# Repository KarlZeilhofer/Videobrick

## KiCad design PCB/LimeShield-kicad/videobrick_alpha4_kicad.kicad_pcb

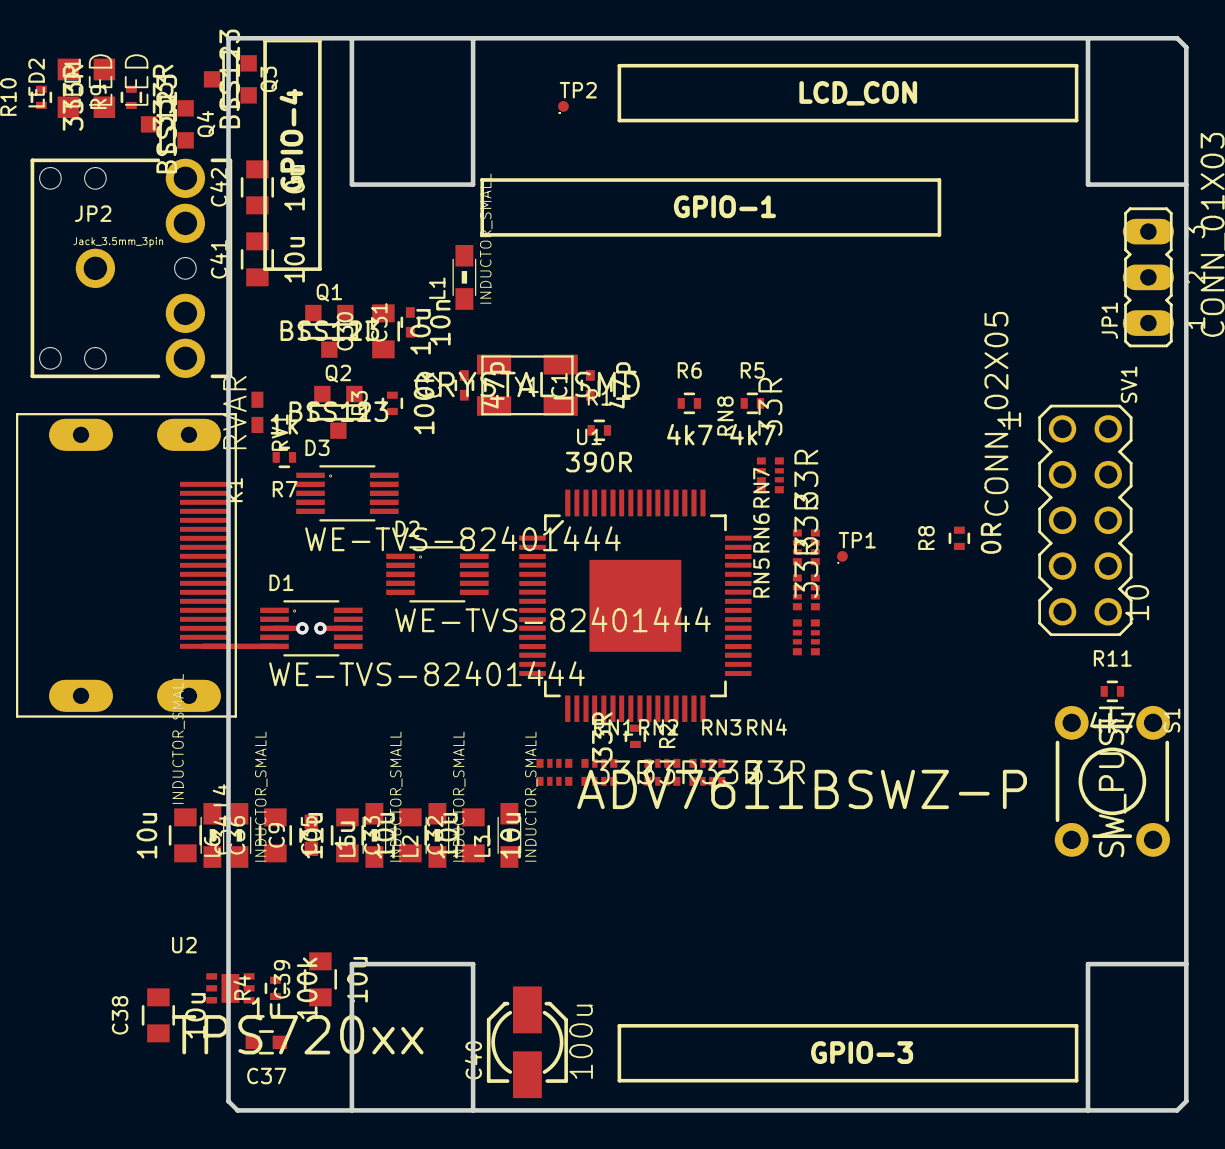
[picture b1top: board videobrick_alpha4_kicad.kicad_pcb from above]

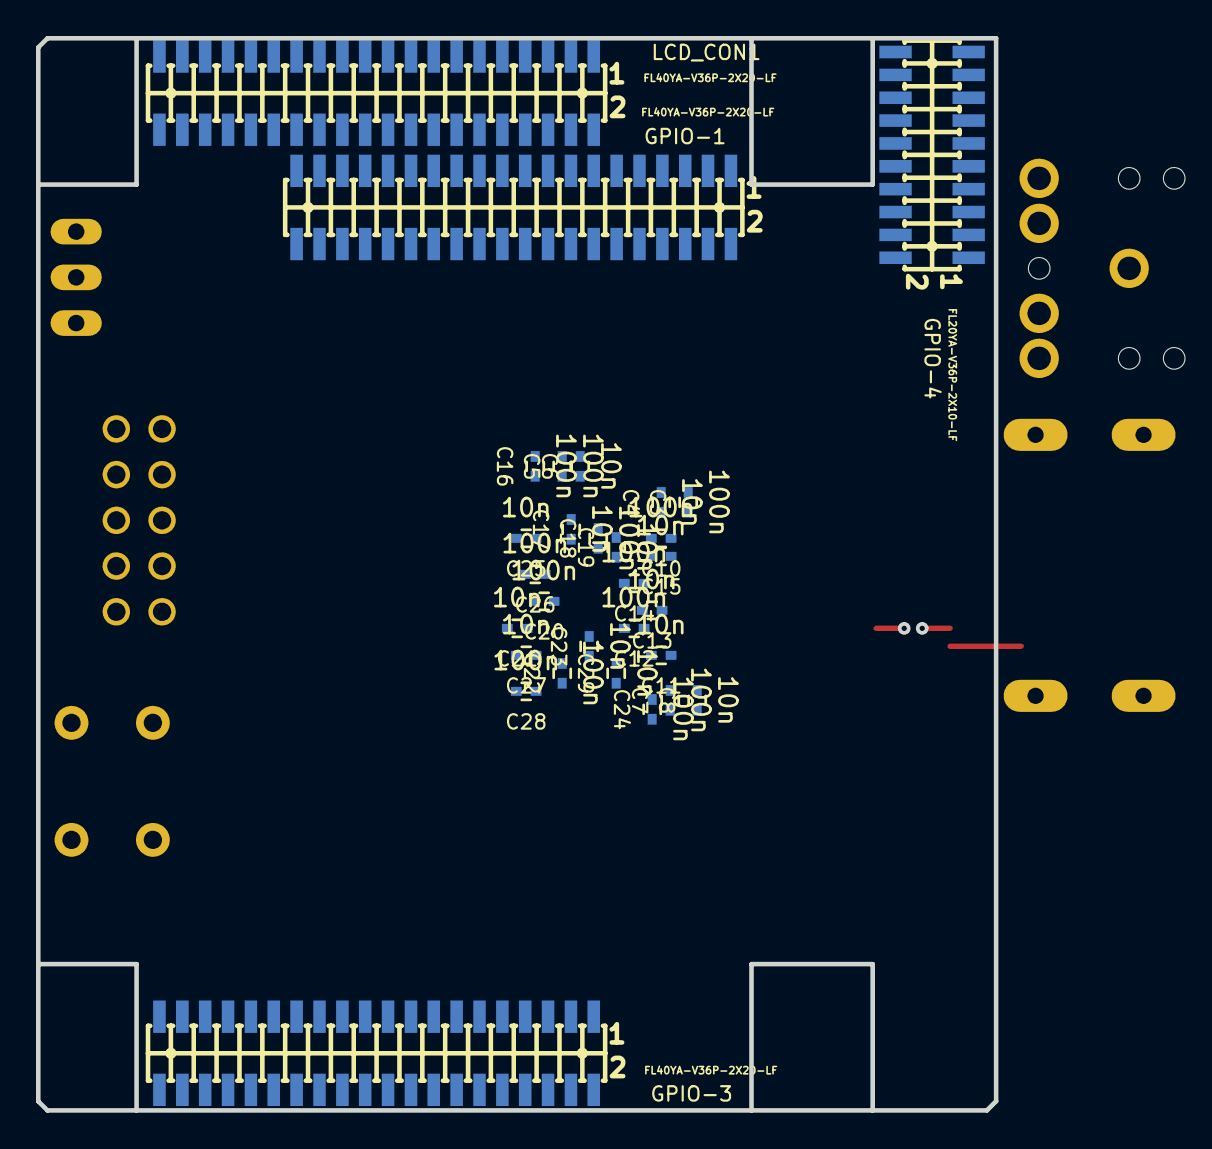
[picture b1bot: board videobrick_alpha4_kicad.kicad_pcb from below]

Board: 4 copper layers, 53.2 x 59.6 mm, 91 parts (30 on the bottom side), 108 nets.

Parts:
C1, C2: 47p; C_0402
C3, C5, C7, C10, C12, C14, C16, C18, C20, C22, C24, C26, C28: 100n; C_0402
C4, C6, C8, C11, C13, C15, C17, C19, C21, C23, C25, C27, C29, C31: 10n; C_0402
C9, C37: 1u; C_0603
C30, C32, C33, C34, C35, C36, C38, C39, C41, C42: 10u; C_0805
C40: 100u; RCL_153CLV-0405
D1, D2, D3: WE-TVS-82401444; WE-TVS_82401444_WE-TVS_MSOP-10L
GPIO-1, GPIO-3: FL40YA-V36P-2X20-LF; A10_OLIMEXINO_LIME_SHIELD_1-YA-V36P-2X20-LF
GPIO-4: FL20YA-V36P-2X10-LF; A10_OLIMEXINO_LIME_SHIELD_1-YA-V36P-2X10-LF
JP1: CONN_01X03; JUMPER_JP2
JP2: Jack_3.5mm_3pin; SPARKFUN-CONNECTORS_AUDIO-JACK
K1: WE-685119134923; INPUTOUTPUTIO_685119134923
L1, L2, L3, L4, L5, L6: INDUCTOR_SMALL; WE-CBF_0805
LCD_CON1: FL40YA-V36P-2X20-LF; A10_OLIMEXINO_LIME_SHIELD_1-YA-V36P-2X20-LF
LED1, LED2: LED; LED_CHIPLED_0805
Q1, Q2, Q3, Q4: BSS123; SOT-23-GDS
R1: 390R; R_0402
R2: 33R; R_0402
R3, R4: 100k; R_0402
R5, R6, R11: 4k7; R_0402
R7: 1k; R_0402
R8: 0R; R_0402
R9, R10: 333R; R_0402
RN1, RN2, RN3, RN4, RN5, RN6, RN7, RN8: 33R; RESISTOR-DIL_4X0402ARV341
RV1: RVAR; WE-VS_WESURGE_0402
S1: SW_PUSH; SPARKFUN-ELECTROMECHANICAL_TACTILE-PTH
SV1: CONN_02X05; CON-LSTB_MA05-2
TP1: TST; TESTPAD_TP06R
TP2: MCLK; TESTPAD_TP06R
U1: ADV7611BSWZ-P; ADI-PHASE-2_QFP50P1200X1200X160-65N
U2: TPS720xx; TEXAS-INSTRUMENTS_BY_ELEMENT14_BATCH_1_SON65P200X200X80-7N
Y1: CRYSTAL_SMD; XTALS_5MM_3.2MM

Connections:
+3.3V: C39.1, D1.3, D2.3, D3.3, GPIO-1.3, GPIO-3.3, GPIO-4.1, L2.1, L3.1, LCD_CON1.3, R4.1, R5.1, R6.1, R9.1, R10.1, R11.1, SV1.10, U2.4, U2.6
+5V: GPIO-1.1, L1.1, LCD_CON1.1
/Connectors/ADV7611_INT: GPIO-3.7, U1.55
/Connectors/ADV7611_RESET: GPIO-1.38, U1.56
/Connectors/ADV7611_SCL: GPIO-1.36, JP1.2, R5.2, U1.53
/Connectors/ADV7611_SDA: GPIO-1.34, JP1.3, R6.2, U1.54
/Connectors/CSI1_D0: GPIO-1.13, RN6.8
/Connectors/CSI1_D1: GPIO-1.15, RN6.7
/Connectors/CSI1_D2: GPIO-1.17, RN6.6
/Connectors/CSI1_D3: GPIO-1.19, RN6.5
/Connectors/CSI1_D4: GPIO-1.21, RN5.8
/Connectors/CSI1_D5: GPIO-1.23, RN5.7
/Connectors/CSI1_D6: GPIO-1.25, RN5.6
/Connectors/CSI1_D7: GPIO-1.27, RN5.5
/Connectors/CSI1_D9: GPIO-3.11, RN4.7
/Connectors/CSI1_D10: GPIO-3.13, RN4.6
/Connectors/CSI1_D11: GPIO-3.15, RN4.5
/Connectors/CSI1_D12: GPIO-3.17, RN3.8
/Connectors/CSI1_D13: GPIO-3.19, RN3.7
/Connectors/CSI1_D14: GPIO-3.21, RN3.6
/Connectors/CSI1_D15: GPIO-3.23, RN3.5
/Connectors/CSI1_D16: GPIO-3.25, RN2.8
/Connectors/CSI1_D17: GPIO-3.27, RN2.7
/Connectors/CSI1_D18: GPIO-3.29, RN2.6
/Connectors/CSI1_D19: GPIO-3.31, RN2.5
/Connectors/CSI1_D20: GPIO-3.33, RN1.8
/Connectors/CSI1_D21: GPIO-3.35, RN1.7
/Connectors/CSI1_D22: GPIO-3.37, RN1.6
/Connectors/CSI1_D23: GPIO-3.39, RN1.5
/Connectors/CSI1_FIELD: GPIO-3.36, R8.2
/Connectors/CSI1_HSYNC: GPIO-1.9, RN7.7
/Connectors/CSI1_MCLK: GPIO-1.7, TP2.TP
/Connectors/CSI1_PCLK: GPIO-1.5, R2.1
/Connectors/CSI1_VSYNC: GPIO-1.11, R8.1, RN7.8
/Connectors/GPIO2: GPIO-4.12, Q3.G
/Connectors/GPIO3: GPIO-4.14, Q4.G
/Connectors/I2S_BCLK: GPIO-3.12, RN8.6
/Connectors/I2S_DI: GPIO-3.22, RN8.5
/Connectors/I2S_LRCK: GPIO-3.14, RN8.7
/Connectors/I2S_MCLK: GPIO-3.10, RN8.8
/Connectors/PB2/PWM0: R11.2, S1.2
CVDD_1V8: C3.1, C4.1, C7.1, C8.1, C9.1, C35.1, L5.2, U1.2, U1.14
DVDDIO_3V3: C24.1, C25.1, C26.1, C27.1, C28.1, C29.1, C32.1, L3.2, U1.23, U1.34, U1.44
DVDD_1V8: C16.1, C17.1, C18.1, C19.1, C20.1, C21.1, C22.1, C23.1, C34.1, L4.1, U1.24, U1.40, U1.52, U1.60
GND: C1.2, C2.2, C3.2, C4.2, C5.2, C6.2, C7.2, C8.2, C9.2, C10.2, C11.2, C12.2, C13.2, C14.2, C15.2, C16.2, C17.2, C18.2, C19.2, C20.2, C21.2, C22.2, C23.2, C24.2, C25.2, C26.2, C27.2, C28.2, C29.2, C30.2, C31.2, C32.2, C33.2, C34.2, C35.2, C36.2, C37.2, C38.2, C39.2, D1.8, D2.8, D3.8, GPIO-1.2, GPIO-3.2, GPIO-3.4, GPIO-4.2, JP1.1, K1.2, K1.5, K1.8, K1.11, K1.17, LCD_CON1.2, LCD_CON1.4, Q1.S, Q2.S, Q3.S, Q4.S, RV1.2, S1.1, SV1.9, U1.65, U2.5, U2.7
HDMI_5V: K1.18, R3.1, R7.2, RV1.1, U1.64
HOT_PLUG_DETECT: D3.1, K1.19, Q2.D, R7.1, U1.1
LINEINL: C42.2, GPIO-4.15
LINEINR: C41.2, GPIO-4.13
unnamed: C37.1, R4.2
unnamed: D1.1, K1.6, U1.9
unnamed: D1.2, K1.4, U1.10
unnamed: D1.4, K1.3, U1.12
unnamed: D1.5, K1.1, U1.13
unnamed: D2.1, K1.12, U1.3
unnamed: D2.2, K1.10, U1.4
unnamed: D2.4, K1.9, U1.6
unnamed: D2.5, K1.7, U1.7
unnamed: D3.2, K1.16, U1.63
unnamed: D3.4, K1.15, U1.62
unnamed: D3.5, K1.13, U1.61
unnamed: Q1.D, Q2.G, R3.2
unnamed: R2.2, U1.25
unnamed: RN1.1, U1.18
unnamed: RN1.2, U1.17
unnamed: RN1.3, U1.16
unnamed: RN1.4, U1.15
unnamed: RN2.1, U1.22
unnamed: RN2.2, U1.21
unnamed: RN2.3, U1.20
unnamed: RN2.4, U1.19
unnamed: RN3.1, U1.29
unnamed: RN3.2, U1.28
unnamed: RN3.3, U1.27
unnamed: RN3.4, U1.26
unnamed: RN4.1, U1.33
unnamed: RN4.2, U1.32
unnamed: RN4.3, U1.31
unnamed: RN4.4, U1.30
unnamed: RN5.1, U1.38
unnamed: RN5.2, U1.37
unnamed: RN5.3, U1.36
unnamed: RN5.4, U1.35
unnamed: RN6.1, U1.43
unnamed: RN6.2, U1.42
unnamed: RN6.3, U1.41
unnamed: RN6.4, U1.39
unnamed: RN7.1, U1.47
unnamed: RN7.2, U1.46
unnamed: RN7.3, U1.45
unnamed: RN8.1, U1.51
unnamed: RN8.2, U1.50
unnamed: RN8.3, U1.49
unnamed: RN8.4, U1.48
PVDD_1V8: C5.1, C6.1, C36.1, L6.2, U1.57
SPI2_CLK: GPIO-1.35, SV1.6
SPI2_CS0: GPIO-1.33, SV1.8
SPI2_MISO: GPIO-1.39, SV1.2
SPI2_MOSI: GPIO-1.37, SV1.4
TVDD_3V3: C10.1, C11.1, C12.1, C13.1, C14.1, C15.1, C33.1, L2.2, U1.5, U1.8, U1.11
TWI2_SCL: GPIO-1.32, SV1.1
TWI2_SDA: GPIO-1.30, SV1.3
UART0_RX: GPIO-1.26, SV1.7
UART0_TX: GPIO-1.28, SV1.5
VDD_1V8: C38.1, L4.2, L5.1, L6.1, U2.1
VDD_5V: C30.1, C31.1, L1.2, Q1.G
XTAL_N: C2.1, R1.2, U1.59
XTAL_P: C1.1, R1.1, U1.58

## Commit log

2015-02-06 Finished schematic, finished placement in PCB, it's just before starting routing
2015-02-06 added GPIO-2 on PCB, most things are unrouted, finished conversion from eagle
